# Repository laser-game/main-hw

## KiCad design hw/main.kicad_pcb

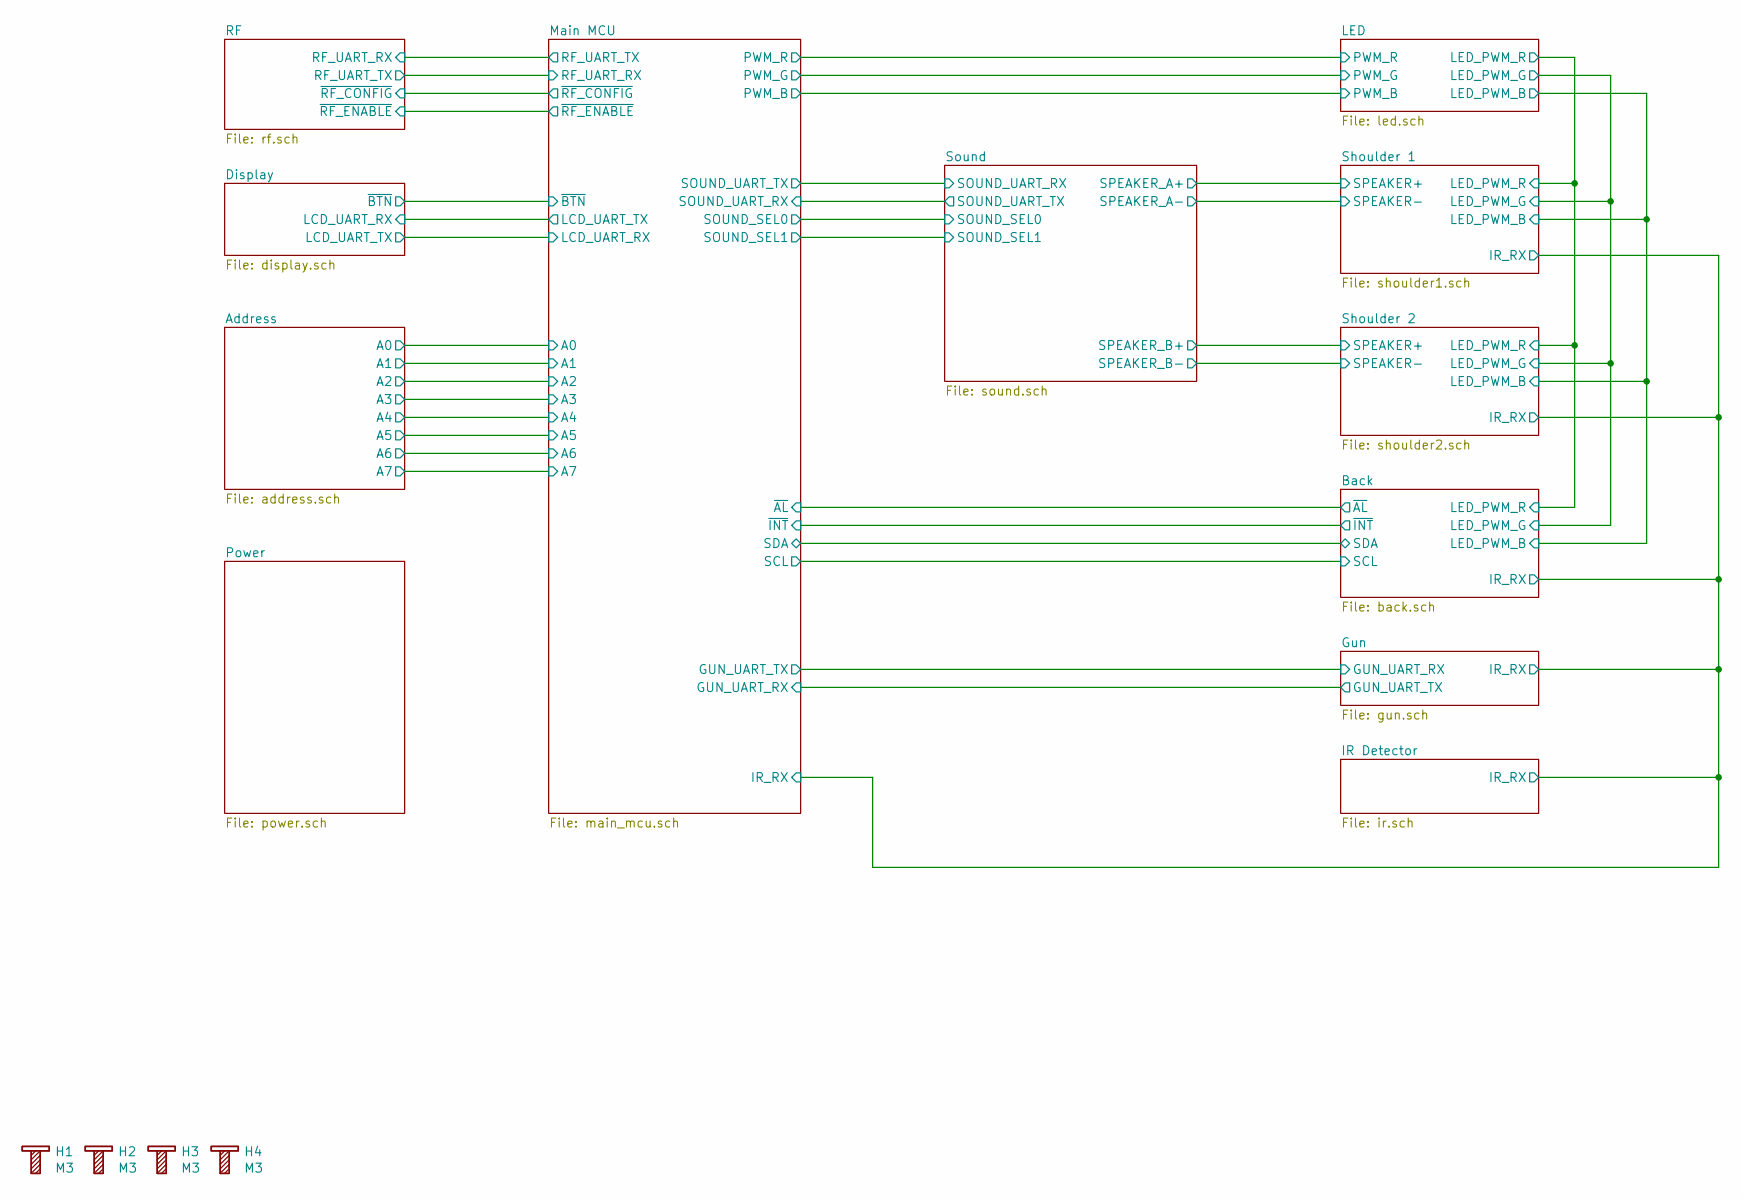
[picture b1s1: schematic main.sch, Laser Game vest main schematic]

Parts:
H1, H2, H3, H4: M3; Bolt_M3

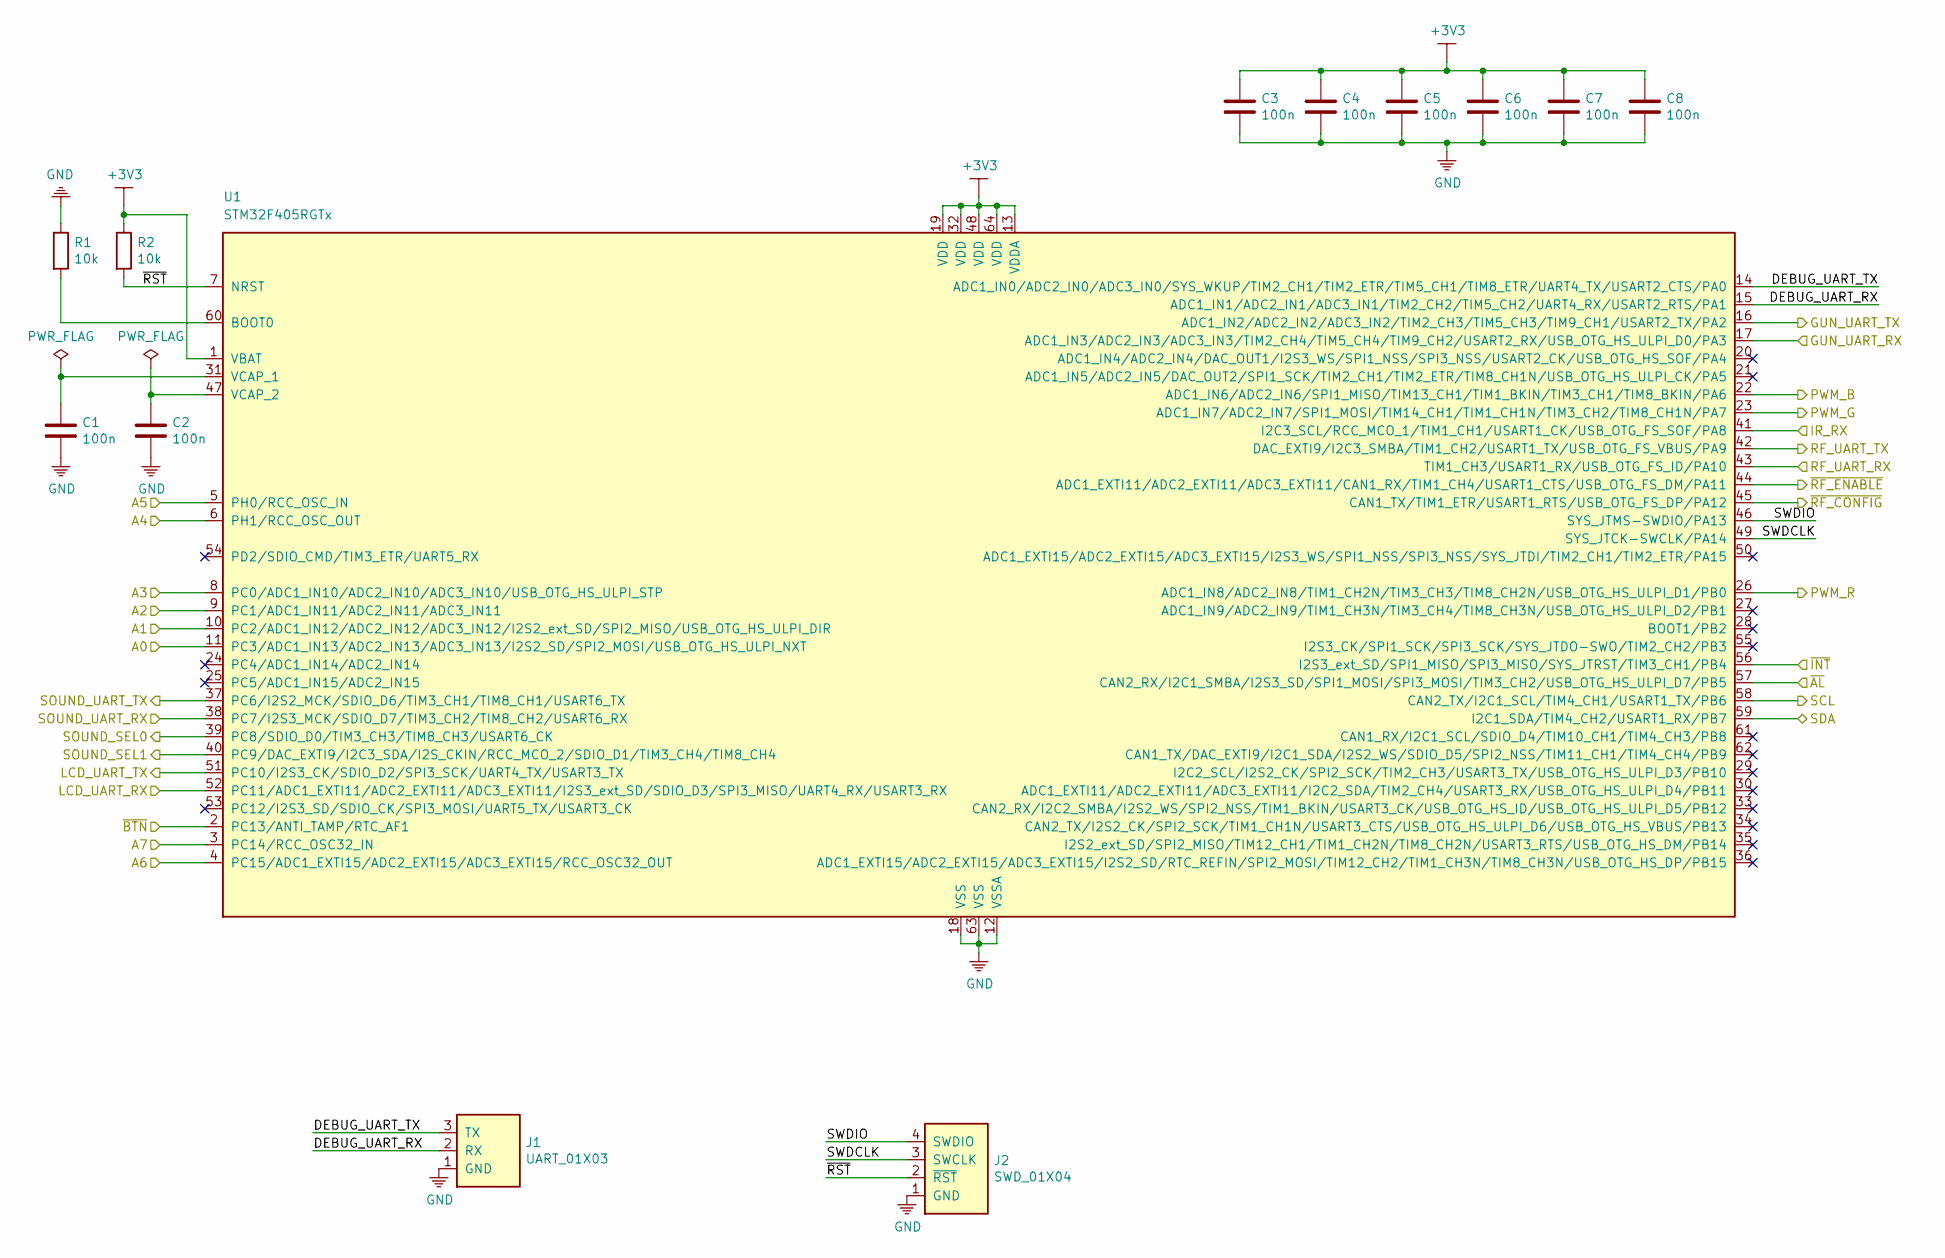
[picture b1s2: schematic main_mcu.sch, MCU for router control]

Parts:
C1, C2, C3, C4, C5, C6, C7, C8: 100n; C_0805_2012Metric
J1: UART_01X03; PinHeader_1x03_P2.54mm_Vertical
J2: SWD_01X04; PinHeader_1x04_P2.54mm_Vertical
R1, R2: 10k; R_0805_2012Metric
U1: STM32F405RGTx; TQFP-64_10x10mm_P0.5mm

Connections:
+3V3: C3.1, C4.1, C5.1, C6.1, C7.1, C8.1, R2.1, U1.1 (VBAT), U1.13 (VDDA), U1.19 (VDD), U1.32 (VDD), U1.48 (VDD), U1.64 (VDD); also elsewhere on the board
/Address/A0: U1.11 (PC3/ADC1_IN13/ADC2_IN13/ADC3_IN13/I2S2_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); also elsewhere on the board
/Address/A1: U1.10 (PC2/ADC1_IN12/ADC2_IN12/ADC3_IN12/I2S2_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); also elsewhere on the board
/Address/A2: U1.9 (PC1/ADC1_IN11/ADC2_IN11/ADC3_IN11); also elsewhere on the board
/Address/A3: U1.8 (PC0/ADC1_IN10/ADC2_IN10/ADC3_IN10/USB_O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); also elsewhere on the board
/Address/A4: U1.6 (PH1/RCC_OSC_OUT); also elsewhere on the board
/Address/A5: U1.5 (PH0/RCC_OSC_IN); also elsewhere on the board
/Address/A6: U1.4 (PC15/ADC1_EXTI15/ADC2_EXTI15/ADC3_EXTI1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); also elsewhere on the board
/Address/A7: U1.3 (PC14/RCC_OSC32_IN); also elsewhere on the board
/Back/IR_RX: U1.41 (I2C3_SCL/RCC_MCO_1/TIM1_CH1/USART1_CK/U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); also elsewhere on the board
/Back/SCL: U1.58 (CAN2_TX/I2C1_SCL/TIM4_CH1/USART1_TX/PB6); also elsewhere on the board
/Back/SDA: U1.59 (I2C1_SDA/TIM4_CH2/USART1_RX/PB7); also elsewhere on the board
/Back/~AL: U1.57 (CAN2_RX/I2C1_SMBA/I2S3_SD/SPI1_MOSI/SPI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); also elsewhere on the board
/Back/~INT: U1.56 (I2S3_ext_SD/SPI1_MISO/SPI3_MISO/SYS_JTR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); also elsewhere on the board
/Display/LCD_UART_RX: U1.51 (PC10/I2S3_CK/SDIO_D2/SPI3_SCK/UART4_TX/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); also elsewhere on the board
/Display/~BTN: U1.2 (PC13/ANTI_TAMP/RTC_AF1); also elsewhere on the board
/Gun/GUN_UART_RX: U1.16 (ADC1_IN2/ADC2_IN2/ADC3_IN2/TIM2_CH3/TIM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); also elsewhere on the board
/LED/PWM_B: U1.22 (ADC1_IN6/ADC2_IN6/SPI1_MISO/TIM13_CH1/T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); also elsewhere on the board
/LED/PWM_G: U1.23 (ADC1_IN7/ADC2_IN7/SPI1_MOSI/TIM14_CH1/T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); also elsewhere on the board
/LED/PWM_R: U1.26 (ADC1_IN8/ADC2_IN8/TIM1_CH2N/TIM3_CH3/TI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); also elsewhere on the board
/Main MCU/DEBUG_UART_RX: J1.2 (RX), U1.15 (ADC1_IN1/ADC2_IN1/ADC3_IN1/TIM2_CH2/TIM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)
/Main MCU/DEBUG_UART_TX: J1.3 (TX), U1.14 (ADC1_IN0/ADC2_IN0/ADC3_IN0/SYS_WKUP/TIM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)
/Main MCU/GUN_UART_RX: U1.17 (ADC1_IN3/ADC2_IN3/ADC3_IN3/TIM2_CH4/TIM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); also elsewhere on the board
/Main MCU/LCD_UART_RX: U1.52 (PC11/ADC1_EXTI11/ADC2_EXTI11/ADC3_EXTI1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); also elsewhere on the board
/Main MCU/RF_UART_RX: U1.43 (TIM1_CH3/USART1_RX/USB_OTG_FS_ID/PA10); also elsewhere on the board
/Main MCU/SOUND_SEL0: U1.39 (PC8/SDIO_D0/TIM3_CH3/TIM8_CH3/USART6_CK); also elsewhere on the board
/Main MCU/SOUND_SEL1: U1.40 (PC9/DAC_EXTI9/I2C3_SDA/I2S_CKIN/RCC_MCO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); also elsewhere on the board
/Main MCU/SOUND_UART_RX: U1.38 (PC7/I2S3_MCK/SDIO_D7/TIM3_CH2/TIM8_CH2/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); also elsewhere on the board
/Main MCU/SWDCLK: J2.3 (SWCLK), U1.49 (SYS_JTCK-SWCLK/PA14)
/Main MCU/SWDIO: J2.4 (SWDIO), U1.46 (SYS_JTMS-SWDIO/PA13)
/Main MCU/~RF_CONFIG: U1.45 (CAN1_TX/TIM1_ETR/USART1_RTS/USB_OTG_FS_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); also elsewhere on the board
/Main MCU/~RF_ENABLE: U1.44 (ADC1_EXTI11/ADC2_EXTI11/ADC3_EXTI11/CAN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); also elsewhere on the board
/Main MCU/~RST: J2.2 (~RST), R2.2, U1.7 (NRST)
/RF/RF_UART_RX: U1.42 (DAC_EXTI9/I2C3_SMBA/TIM1_CH2/USART1_TX/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); also elsewhere on the board
/Sound/SOUND_UART_RX: U1.37 (PC6/I2S2_MCK/SDIO_D6/TIM3_CH1/TIM8_CH1/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); also elsewhere on the board
GND: C1.2, C2.2, C3.2, C4.2, C5.2, C6.2, C7.2, C8.2, J1.1 (GND), J2.1 (GND), R1.1, U1.12 (VSSA), U1.18 (VSS), U1.63 (VSS); also elsewhere on the board
unnamed: C1.1, U1.31 (VCAP_1)
unnamed: C2.1, U1.47 (VCAP_2)
unnamed: R1.2, U1.60 (BOOT0)

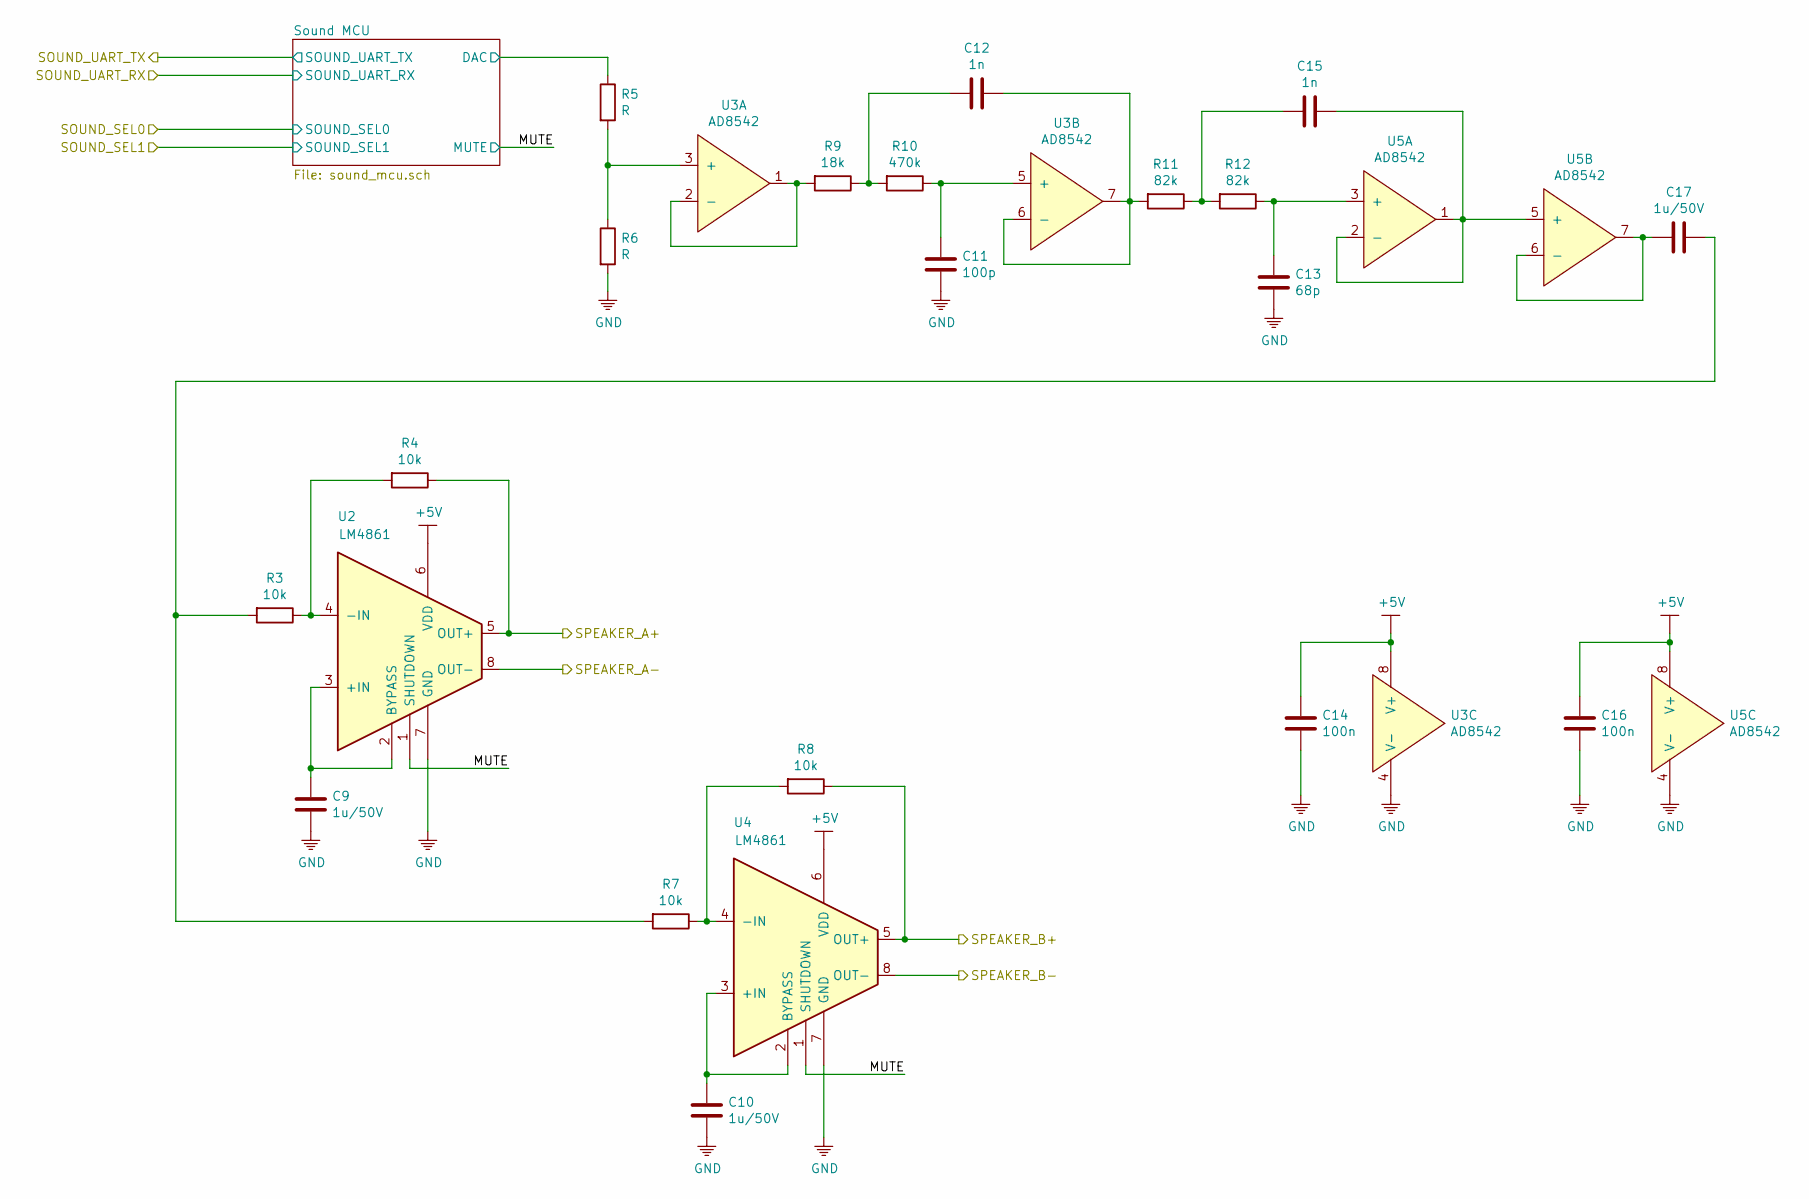
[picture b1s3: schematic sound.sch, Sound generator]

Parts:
C9, C10, C17: 1u/50V; C_0805_2012Metric
C11: 100p; C_0805_2012Metric
C12, C15: 1n; C_0805_2012Metric
C13: 68p; C_0805_2012Metric
C14, C16: 100n; C_0805_2012Metric
R3, R4, R7, R8: 10k; R_0805_2012Metric
R5, R6: R; R_0805_2012Metric
R9: 18k; R_0805_2012Metric
R10: 470k; R_0805_2012Metric
R11, R12: 82k; R_0805_2012Metric
U2, U4: LM4861; SOIJ-8_5.3x5.3mm_P1.27mm
U3, U5: AD8542; SOIJ-8_5.3x5.3mm_P1.27mm

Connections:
+5V: C14.1, C16.1, U2.6 (VDD), U3.8 (V+), U4.6 (VDD), U5.8 (V+); also elsewhere on the board
/Shoulder 1/SPEAKER+: R4.1, U2.5 (OUT+); also elsewhere on the board
/Shoulder 1/SPEAKER-: U2.8 (OUT-); also elsewhere on the board
/Shoulder 2/SPEAKER+: R8.1, U4.5 (OUT+); also elsewhere on the board
/Shoulder 2/SPEAKER-: U4.8 (OUT-); also elsewhere on the board
/Sound/MUTE: U2.1 (SHUTDOWN), U4.1 (SHUTDOWN); also elsewhere on the board
/Sound/Sound MCU/DAC: R5.1; also elsewhere on the board
GND: C9.2, C10.2, C11.2, C13.2, C14.2, C16.2, R6.2, U2.7 (GND), U3.4 (V-), U4.7 (GND), U5.4 (V-); also elsewhere on the board
unnamed: C9.1, U2.2 (BYPASS), U2.3 (+IN)
unnamed: C10.1, U4.2 (BYPASS), U4.3 (+IN)
unnamed: C11.1, R10.1, U3.5 (+)
unnamed: C12.1, R9.1, R10.2
unnamed: C12.2, R11.2, U3.6 (-), U3.7
unnamed: C13.1, R12.1, U5.3 (+)
unnamed: C15.1, R11.1, R12.2
unnamed: C15.2, U5.1, U5.2 (-), U5.5 (+)
unnamed: C17.1, R3.2, R7.2
unnamed: C17.2, U5.6 (-), U5.7
unnamed: R3.1, R4.2, U2.4 (-IN)
unnamed: R5.2, R6.1, U3.3 (+)
unnamed: R7.1, R8.2, U4.4 (-IN)
unnamed: R9.2, U3.1, U3.2 (-)

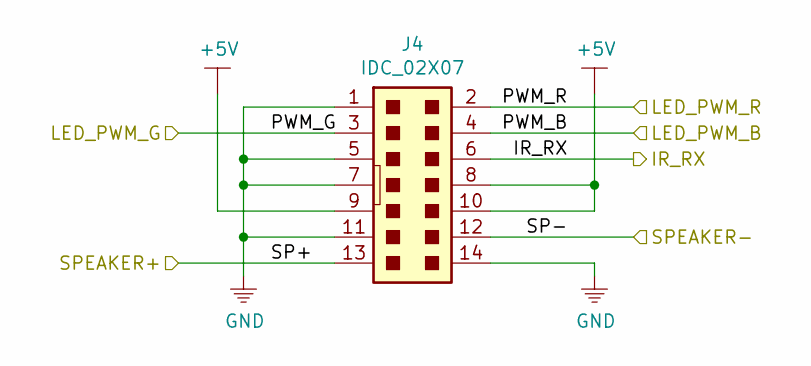
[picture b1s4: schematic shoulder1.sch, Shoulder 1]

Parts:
J4: IDC_02X07; IDC-Header_2x07_P2.54mm_Vertical

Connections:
+5V: J4.8, J4.9, J4.10; also elsewhere on the board
/Back/IR_RX: J4.6; also elsewhere on the board
/Back/LED_PWM_B: J4.4; also elsewhere on the board
/Back/LED_PWM_G: J4.3; also elsewhere on the board
/Back/LED_PWM_R: J4.2; also elsewhere on the board
/Shoulder 1/SPEAKER+: J4.13; also elsewhere on the board
/Shoulder 1/SPEAKER-: J4.12; also elsewhere on the board
GND: J4.1, J4.5, J4.7, J4.11, J4.14; also elsewhere on the board

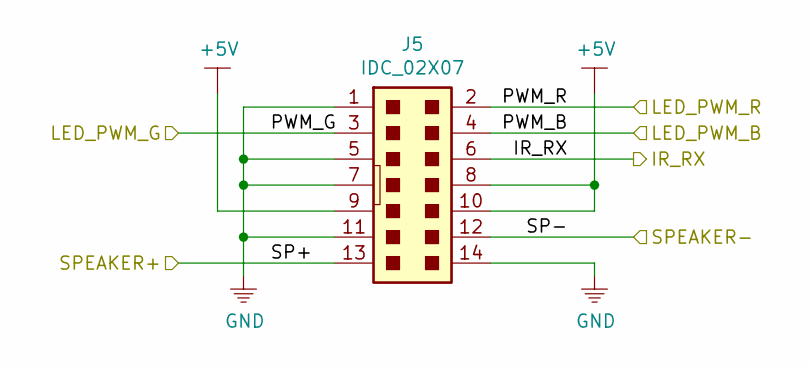
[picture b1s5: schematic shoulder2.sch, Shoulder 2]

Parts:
J5: IDC_02X07; IDC-Header_2x07_P2.54mm_Vertical

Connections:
+5V: J5.8, J5.9, J5.10; also elsewhere on the board
/Back/IR_RX: J5.6; also elsewhere on the board
/Back/LED_PWM_B: J5.4; also elsewhere on the board
/Back/LED_PWM_G: J5.3; also elsewhere on the board
/Back/LED_PWM_R: J5.2; also elsewhere on the board
/Shoulder 2/SPEAKER+: J5.13; also elsewhere on the board
/Shoulder 2/SPEAKER-: J5.12; also elsewhere on the board
GND: J5.1, J5.5, J5.7, J5.11, J5.14; also elsewhere on the board

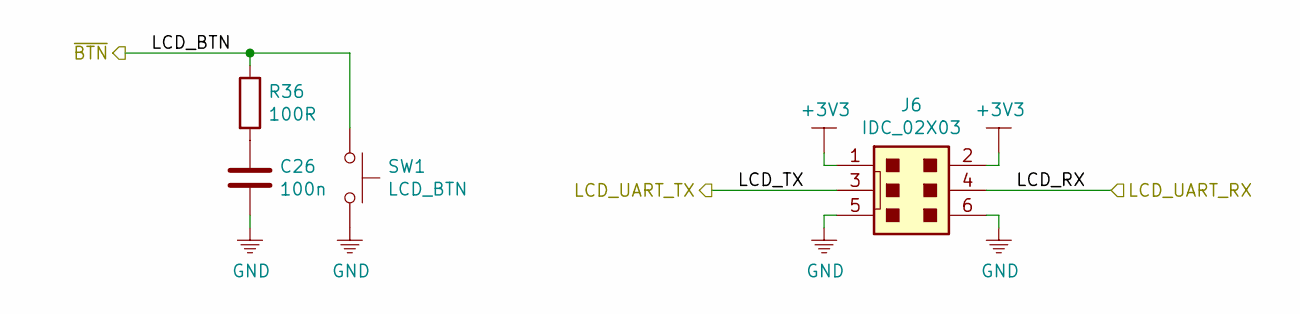
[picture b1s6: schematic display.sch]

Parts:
C26: 100n; C_0805_2012Metric
J6: IDC_02X03; IDC-Header_2x03_P2.54mm_Vertical
R36: 100R; R_0805_2012Metric
SW1: LCD_BTN; SW_SPST_FSMSM

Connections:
+3V3: J6.1, J6.2; also elsewhere on the board
/Display/LCD_UART_RX: J6.4; also elsewhere on the board
/Display/~BTN: R36.1, SW1.1; also elsewhere on the board
/Main MCU/LCD_UART_RX: J6.3; also elsewhere on the board
GND: C26.2, J6.5, J6.6, SW1.2; also elsewhere on the board
unnamed: C26.1, R36.2

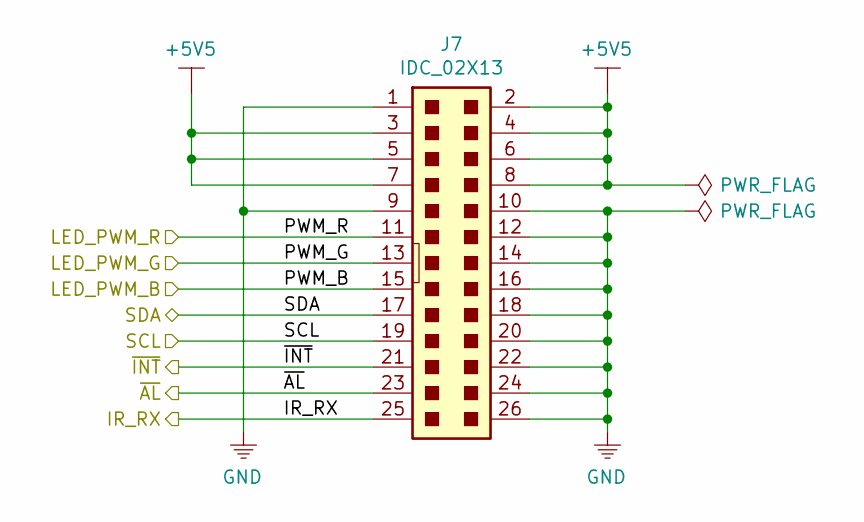
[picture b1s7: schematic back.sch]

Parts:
J7: IDC_02X13; IDC-Header_2x13_P2.54mm_Vertical

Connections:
+5V5: J7.2, J7.3, J7.4, J7.5, J7.6, J7.7, J7.8; also elsewhere on the board
/Back/IR_RX: J7.25; also elsewhere on the board
/Back/LED_PWM_B: J7.15; also elsewhere on the board
/Back/LED_PWM_G: J7.13; also elsewhere on the board
/Back/LED_PWM_R: J7.11; also elsewhere on the board
/Back/SCL: J7.19; also elsewhere on the board
/Back/SDA: J7.17; also elsewhere on the board
/Back/~AL: J7.23; also elsewhere on the board
/Back/~INT: J7.21; also elsewhere on the board
GND: J7.1, J7.9, J7.10, J7.12, J7.14, J7.16, J7.18, J7.20, J7.22, J7.24, J7.26; also elsewhere on the board

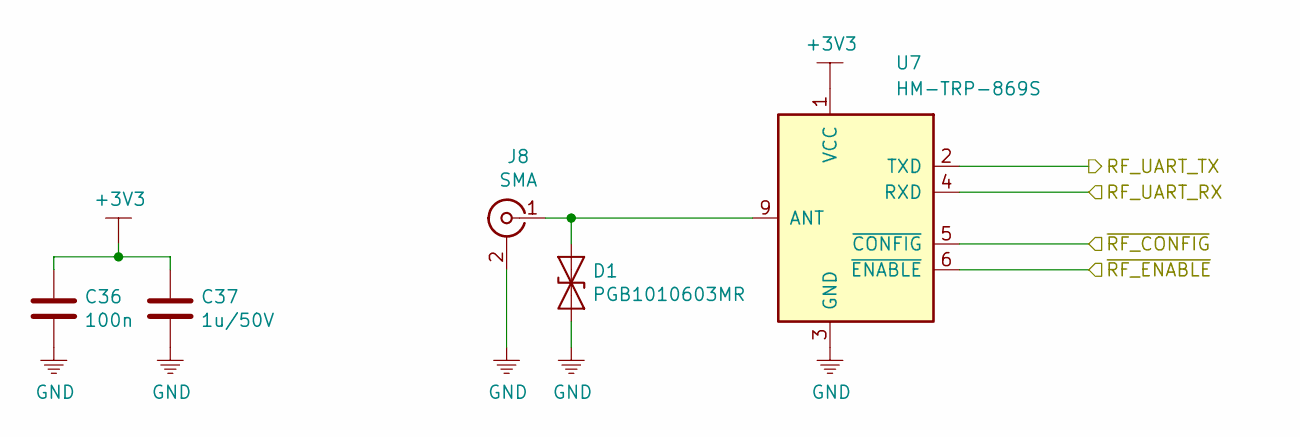
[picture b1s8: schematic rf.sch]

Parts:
C36: 100n; C_0805_2012Metric
C37: 1u/50V; C_0805_2012Metric
D1: PGB1010603MR; D_0603_1608Metric
J8: SMA; SMA_Jack_Vertical
U7: HM-TRP-869S; HM-TRP-SMD

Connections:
+3V3: C36.1, C37.1, U7.1 (VCC); also elsewhere on the board
/Main MCU/RF_UART_RX: U7.2 (TXD); also elsewhere on the board
/Main MCU/~RF_CONFIG: U7.5 (~CONFIG); also elsewhere on the board
/Main MCU/~RF_ENABLE: U7.6 (~ENABLE); also elsewhere on the board
/RF/RF_UART_RX: U7.4 (RXD); also elsewhere on the board
GND: C36.2, C37.2, D1.2 (A2), J8.2 (Ext), U7.3 (GND), U7.8 (GND); also elsewhere on the board
unnamed: D1.1 (A1), J8.1 (In), U7.9 (ANT)

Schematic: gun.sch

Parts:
C38, C39: 100n; C_0805_2012Metric
J9: IDC_02X05; IDC-Header_2x05_P2.54mm_Vertical
U12, U13: 74AHC1G08; SOT-23-5

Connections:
+5V: C38.1, C39.1, U12.5 (VCC), U13.5 (VCC); also elsewhere on the board
+5V5: J9.1, J9.2; also elsewhere on the board
/Back/IR_RX: J9.3, J9.4; also elsewhere on the board
/Gun/GUN_RX: J9.5, J9.6, U12.4 (Y)
/Gun/GUN_TX: J9.7, J9.8, U13.1 (A), U13.2 (B)
/Gun/GUN_UART_RX: U12.1 (A), U12.2 (B); also elsewhere on the board
/Main MCU/GUN_UART_RX: U13.4 (Y); also elsewhere on the board
GND: C38.2, C39.2, J9.9, J9.10, U12.3 (GND), U13.3 (GND); also elsewhere on the board

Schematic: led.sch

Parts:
D2, D3, D4, D5: LTST-G563ZEGBW; LED_RGB_5050-6
R15, R16, R18, R19, R21, R22, R24, R25: 120R; R_0805_2012Metric
R17, R20, R23, R26: 180R; R_0805_2012Metric
U8: ULN2003; SOIC-16_3.9x9.9mm_P1.27mm

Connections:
+5V: D2.4 (BA), D2.5 (GA), D2.6 (RA), D3.4 (BA), D3.5 (GA), D3.6 (RA), D4.4 (BA), D4.5 (GA), D4.6 (RA), D5.4 (BA), D5.5 (GA), D5.6 (RA), U8.9 (COM); also elsewhere on the board
/Back/LED_PWM_B: R15.2, R18.2, R21.2, R24.2, U8.10 (O7), U8.11 (O6), U8.12 (O5); also elsewhere on the board
/Back/LED_PWM_G: R16.2, R19.2, R22.2, R25.2, U8.13 (O4), U8.14 (O3); also elsewhere on the board
/Back/LED_PWM_R: R17.2, R20.2, R23.2, R26.2, U8.15 (O2), U8.16 (O1); also elsewhere on the board
/LED/PWM_B: U8.5 (I5), U8.6 (I6), U8.7 (I7); also elsewhere on the board
/LED/PWM_G: U8.3 (I3), U8.4 (I4); also elsewhere on the board
/LED/PWM_R: U8.1 (I1), U8.2 (I2); also elsewhere on the board
GND: U8.8 (GND); also elsewhere on the board
unnamed: D2.1 (RK), R15.1
unnamed: D2.2 (GK), R16.1
unnamed: D2.3 (BK), R17.1
unnamed: D3.1 (RK), R18.1
unnamed: D3.2 (GK), R19.1
unnamed: D3.3 (BK), R20.1
unnamed: D4.1 (RK), R21.1
unnamed: D4.2 (GK), R22.1
unnamed: D4.3 (BK), R23.1
unnamed: D5.1 (RK), R24.1
unnamed: D5.2 (GK), R25.1
unnamed: D5.3 (BK), R26.1

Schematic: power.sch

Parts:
C27, C30, C31, C34: 1u/50V; C_0805_2012Metric
C28, C29, C32, C33: 100n; C_0805_2012Metric
U9, U10: MCP1826S; SOT-223-3_TabPin2

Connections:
+3V3: C33.1, C34.1, U10.3 (VO); also elsewhere on the board
+5V: C29.1, C30.1, C31.1, C32.1, U9.3 (VO), U10.1 (VI); also elsewhere on the board
+5V5: C27.1, C28.1, U9.1 (VI); also elsewhere on the board
GND: C27.2, C28.2, C29.2, C30.2, C31.2, C32.2, C33.2, C34.2, U9.2 (GND), U10.2 (GND); also elsewhere on the board

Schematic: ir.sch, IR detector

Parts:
C35: 47u/10V; CP_EIA-3528-21_Kemet-B
R27: 100R; R_0805_2012Metric
U11: OSRB38C9BA; OSRB8C9BA_Horizontal

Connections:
+5V: R27.1; also elsewhere on the board
/Back/IR_RX: U11.1 (OUT); also elsewhere on the board
GND: C35.2, U11.2 (GND); also elsewhere on the board
unnamed: C35.1, R27.2, U11.3 (VCC)

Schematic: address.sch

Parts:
R28, R29, R30, R31, R32, R33, R34, R35: 10k; R_0805_2012Metric

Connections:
/Address/A0: R35.1; also elsewhere on the board
/Address/A1: R34.1; also elsewhere on the board
/Address/A2: R33.1; also elsewhere on the board
/Address/A3: R32.1; also elsewhere on the board
/Address/A4: R31.1; also elsewhere on the board
/Address/A5: R30.1; also elsewhere on the board
/Address/A6: R29.1; also elsewhere on the board
/Address/A7: R28.1; also elsewhere on the board
GND: R28.2, R29.2, R30.2, R31.2, R32.2, R33.2, R34.2, R35.2; also elsewhere on the board

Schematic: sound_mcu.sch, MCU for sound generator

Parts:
C18, C19, C20, C21, C22, C23, C24, C25: 100n; C_0805_2012Metric
J3: SWD_01X04; PinHeader_1x04_P2.54mm_Vertical
R13, R14: 10k; R_0805_2012Metric
U6: STM32F405RGTx; TQFP-64_10x10mm_P0.5mm

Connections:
+3V3: C20.1, C21.1, C22.1, C23.1, C24.1, C25.1, R14.1, U6.1 (VBAT), U6.13 (VDDA), U6.19 (VDD), U6.32 (VDD), U6.48 (VDD), U6.64 (VDD); also elsewhere on the board
/Main MCU/SOUND_SEL0: U6.44 (ADC1_EXTI11/ADC2_EXTI11/ADC3_EXTI11/CAN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); also elsewhere on the board
/Main MCU/SOUND_SEL1: U6.45 (CAN1_TX/TIM1_ETR/USART1_RTS/USB_OTG_FS_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); also elsewhere on the board
/Main MCU/SOUND_UART_RX: U6.42 (DAC_EXTI9/I2C3_SMBA/TIM1_CH2/USART1_TX/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); also elsewhere on the board
/Sound/MUTE: U6.22 (ADC1_IN6/ADC2_IN6/SPI1_MISO/TIM13_CH1/T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); also elsewhere on the board
/Sound/SOUND_UART_RX: U6.43 (TIM1_CH3/USART1_RX/USB_OTG_FS_ID/PA10); also elsewhere on the board
/Sound/Sound MCU/DAC: U6.20 (ADC1_IN4/ADC2_IN4/DAC_OUT1/I2S3_WS/SPI1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); also elsewhere on the board
/Sound/Sound MCU/SWDCLK: J3.3 (SWCLK), U6.49 (SYS_JTCK-SWCLK/PA14)
/Sound/Sound MCU/SWDIO: J3.4 (SWDIO), U6.46 (SYS_JTMS-SWDIO/PA13)
/Sound/Sound MCU/~RST: J3.2 (~RST), R14.2, U6.7 (NRST)
GND: C18.2, C19.2, C20.2, C21.2, C22.2, C23.2, C24.2, C25.2, J3.1 (GND), R13.1, U6.12 (VSSA), U6.18 (VSS), U6.63 (VSS); also elsewhere on the board
unnamed: C18.1, U6.31 (VCAP_1)
unnamed: C19.1, U6.47 (VCAP_2)
unnamed: R13.2, U6.60 (BOOT0)

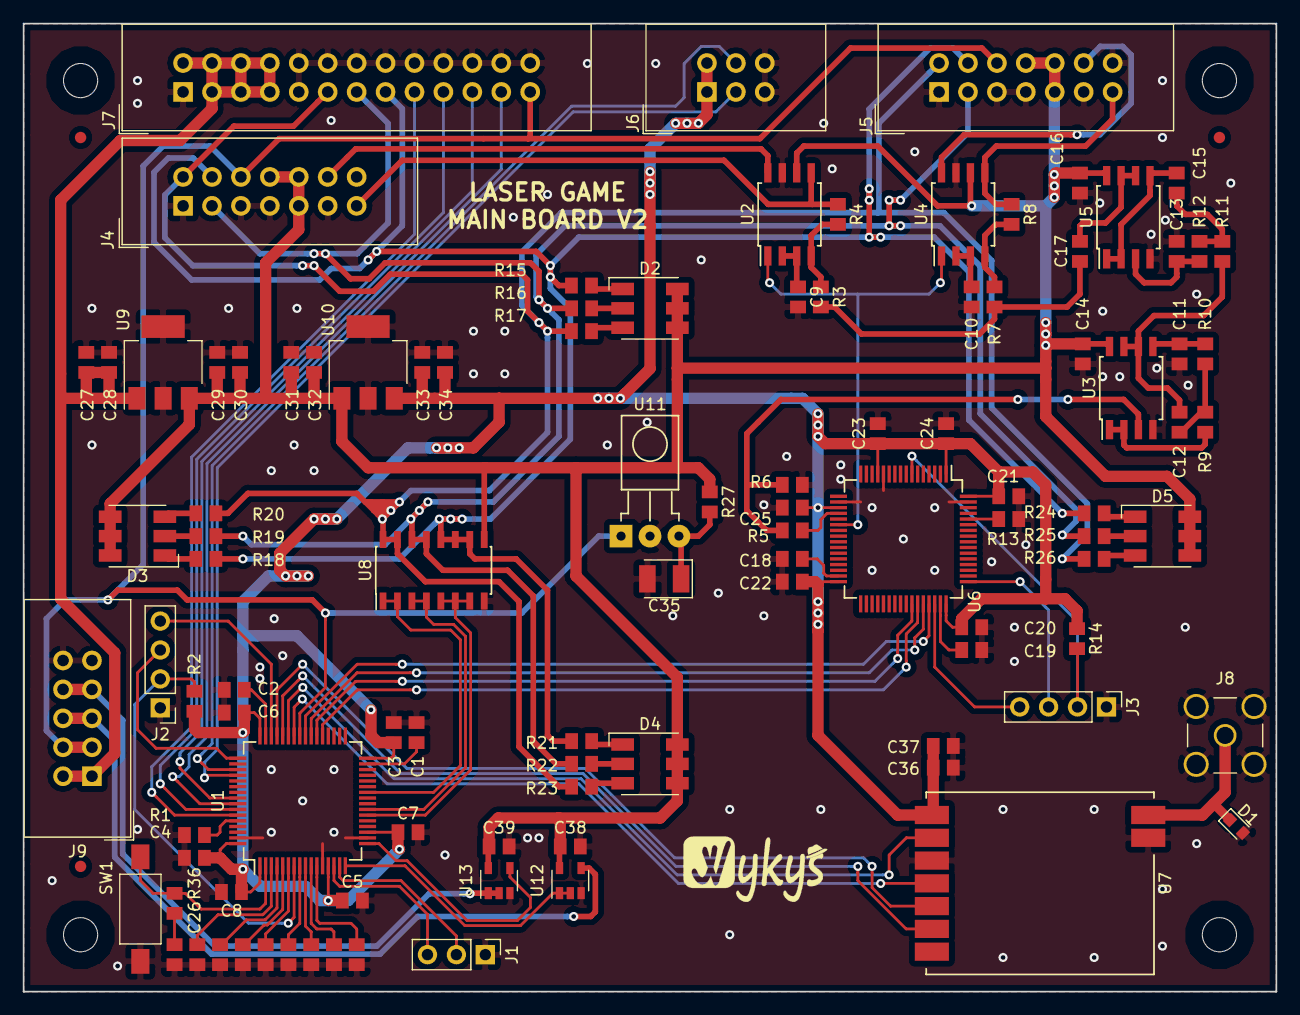
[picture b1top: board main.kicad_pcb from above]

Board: 2 copper layers, 110.0 x 85.0 mm, 107 parts (0 on the bottom side), 87 nets.

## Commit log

2018-03-30 added license and updated readme
2018-04-11 updated gitignore added pdf
2018-04-11 added schematic sound generator
2018-04-12 finished schematic
2018-04-12 removed charger.sch
2018-04-15 updated schematic added footptints
2018-04-16 updated schematic
2018-04-16 placement component to pcb
2018-04-16 updated schematic added buffer to gun uart and updated pcb
2018-04-16 updated pcb placement
2018-04-16 updated pcb
2018-04-20 removed LCD RST signal
2018-04-20 updated button RC filter
2018-04-20 added fiducials
2018-05-02 added boom file and schematic for fabracation
2018-05-08 added placement files
